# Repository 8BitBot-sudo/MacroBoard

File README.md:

# MacroBoard

So, this is a 12-button and 1 rotary switch macro board. This is useful for clicking on one button for repetitive tasks or for quickly opening an app. The rotary switch would be for controlling volume

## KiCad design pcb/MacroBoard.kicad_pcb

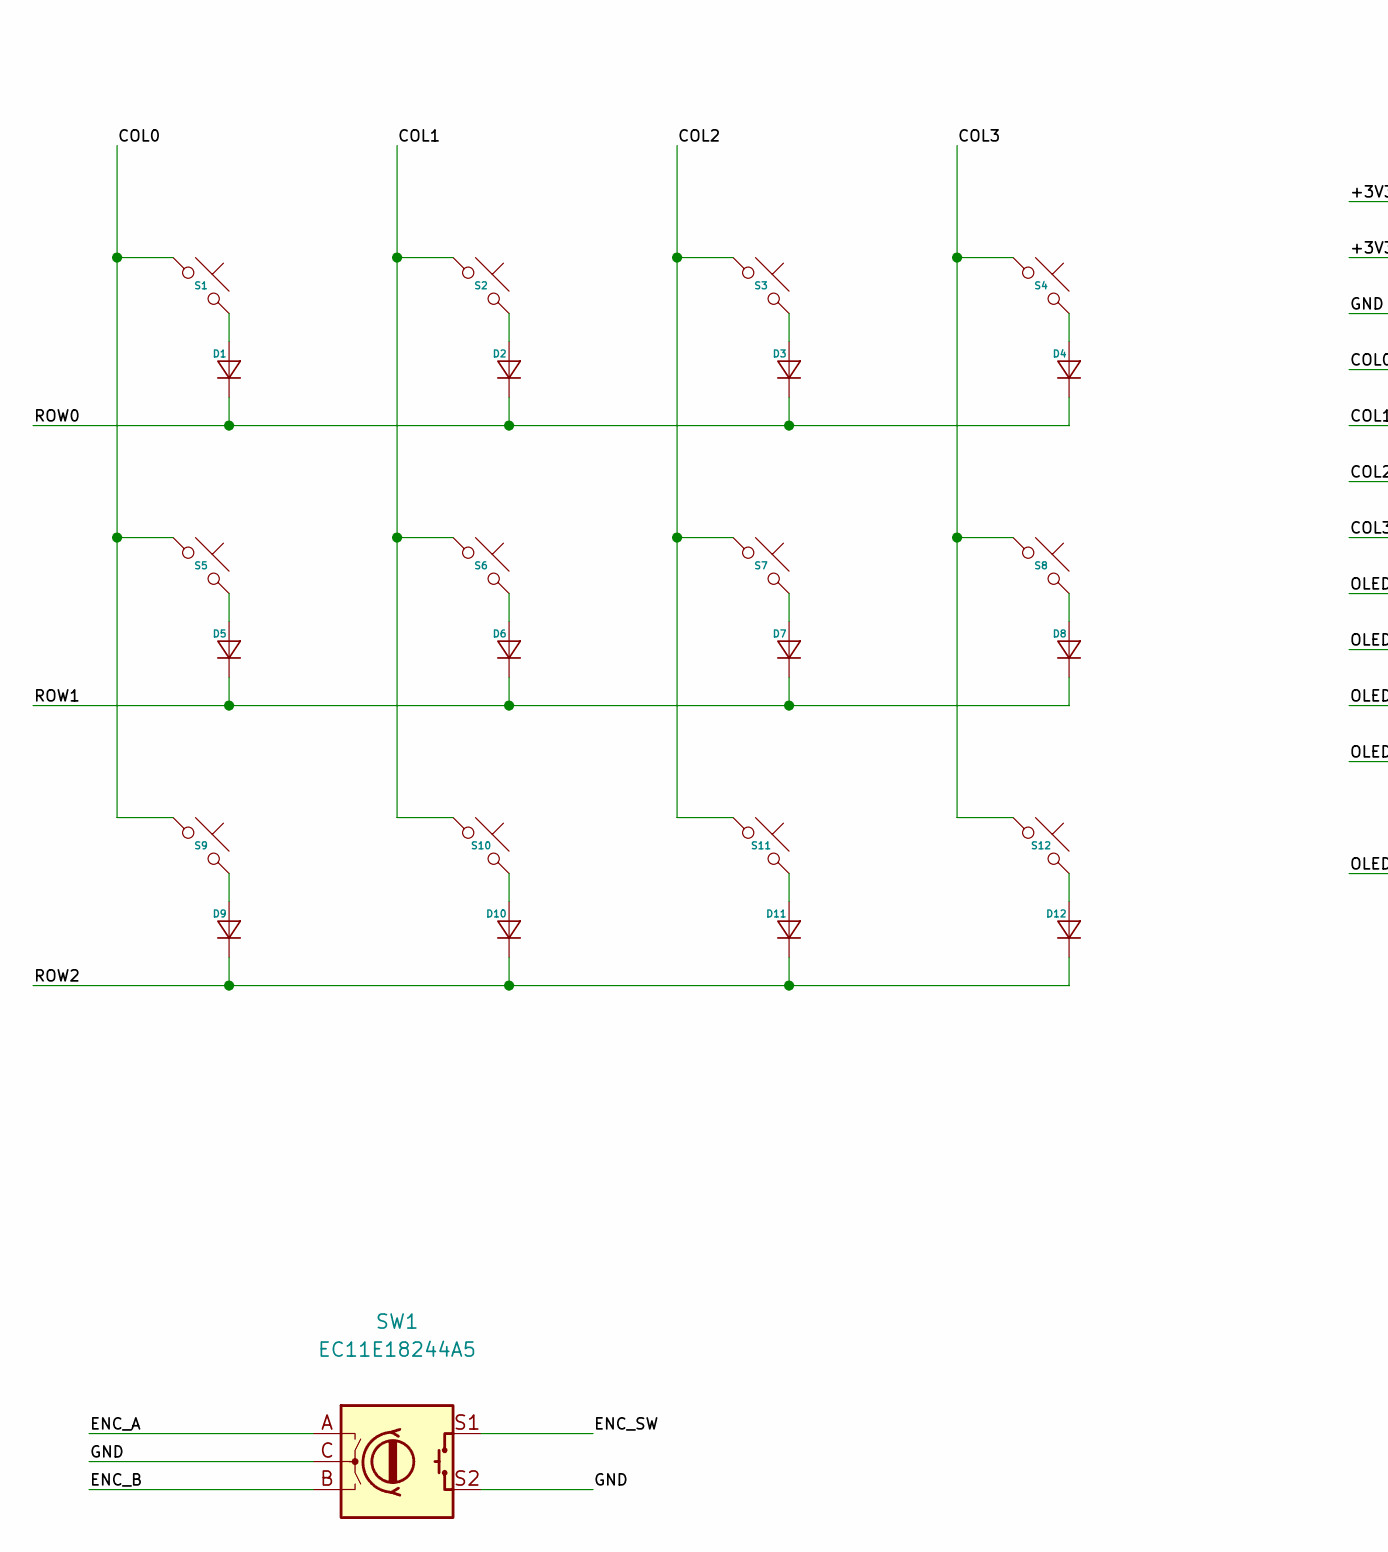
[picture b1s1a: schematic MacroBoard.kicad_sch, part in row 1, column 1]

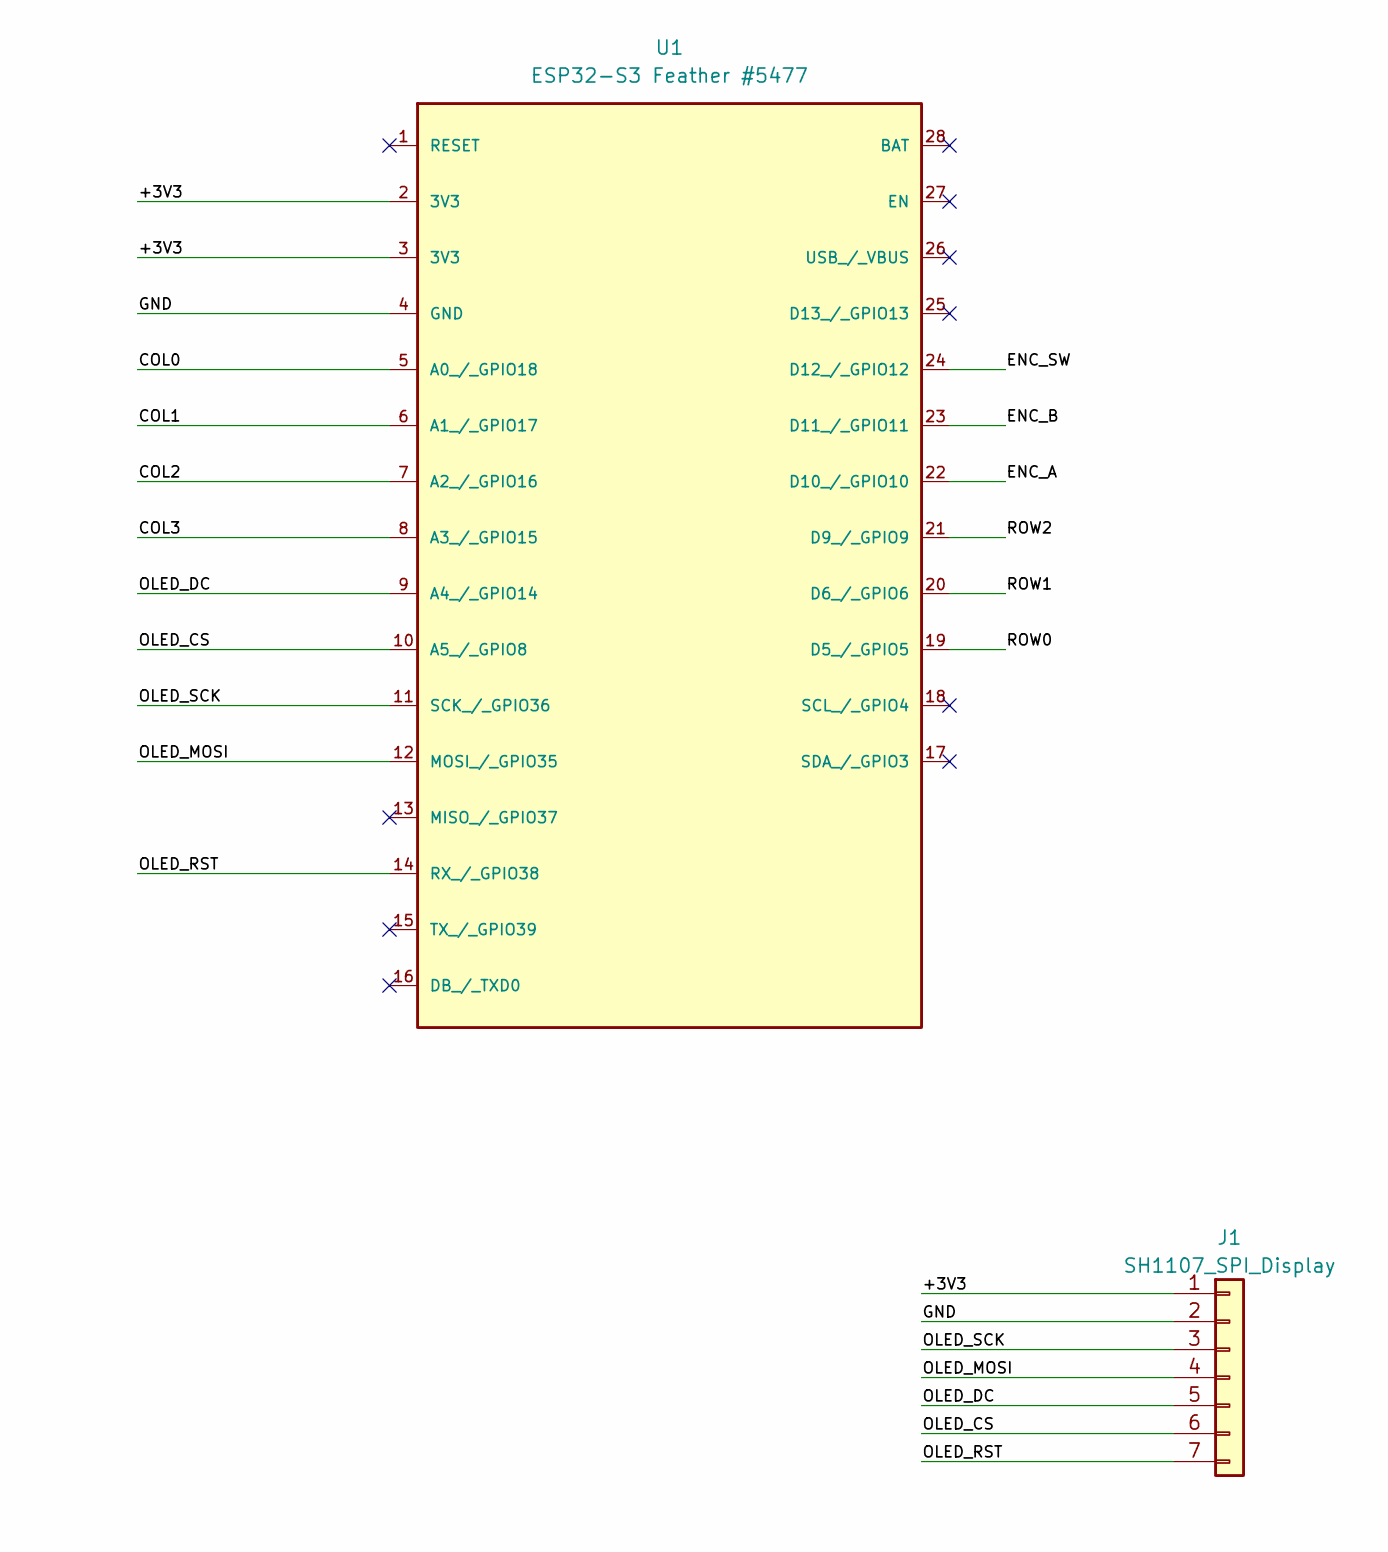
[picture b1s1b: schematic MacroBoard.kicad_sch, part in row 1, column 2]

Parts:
D1, D2, D3, D4, D5, D6, D7, D8, D9, D10, D11, D12: 1N4148; D_DO-35_SOD27_P7.62mm_Horizontal
J1: SH1107_SPI_Display; PinHeader_1x07_P2.54mm_Vertical
S1, S2, S3, S4, S5, S6, S7, S8, S9, S10, S11, S12: Cherry_MX; SW_Cherry_MX_1.00u_PCB
SW1: EC11E18244A5; RotaryEncoder_Alps_EC11E-Switch_Vertical_H20mm
U1: ESP32-S3 Feather #5477; Adafruit_Feather

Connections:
/+3V3: J1.1, U1.2 (3V3), U1.3 (3V3)
/COL0: S1.1, S5.1, S9.1, U1.5 (A0_/_GPIO18)
/COL1: S2.1, S6.1, S10.1, U1.6 (A1_/_GPIO17)
/COL2: S3.1, S7.1, S11.1, U1.7 (A2_/_GPIO16)
/COL3: S4.1, S8.1, S12.1, U1.8 (A3_/_GPIO15)
/ENC_A: SW1.A, U1.22 (D10_/_GPIO10)
/ENC_B: SW1.B, U1.23 (D11_/_GPIO11)
/ENC_SW: SW1.S1, U1.24 (D12_/_GPIO12)
/GND: J1.2, SW1.C, SW1.S2, U1.4 (GND)
/OLED_CS: J1.6, U1.10 (A5_/_GPIO8)
/OLED_DC: J1.5, U1.9 (A4_/_GPIO14)
/OLED_MOSI: J1.4, U1.12 (MOSI_/_GPIO35)
/OLED_RST: J1.7, U1.14 (RX_/_GPIO38)
/OLED_SCK: J1.3, U1.11 (SCK_/_GPIO36)
/ROW0: D1.1 (K), D2.1 (K), D3.1 (K), D4.1 (K), U1.19 (D5_/_GPIO5)
/ROW1: D5.1 (K), D6.1 (K), D7.1 (K), D8.1 (K), U1.20 (D6_/_GPIO6)
/ROW2: D9.1 (K), D10.1 (K), D11.1 (K), D12.1 (K), U1.21 (D9_/_GPIO9)
unnamed: D1.2 (A), S1.2
unnamed: D2.2 (A), S2.2
unnamed: D3.2 (A), S3.2
unnamed: D4.2 (A), S4.2
unnamed: D5.2 (A), S5.2
unnamed: D6.2 (A), S6.2
unnamed: D7.2 (A), S7.2
unnamed: D8.2 (A), S8.2
unnamed: D9.2 (A), S9.2
unnamed: D10.2 (A), S10.2
unnamed: D11.2 (A), S11.2
unnamed: D12.2 (A), S12.2

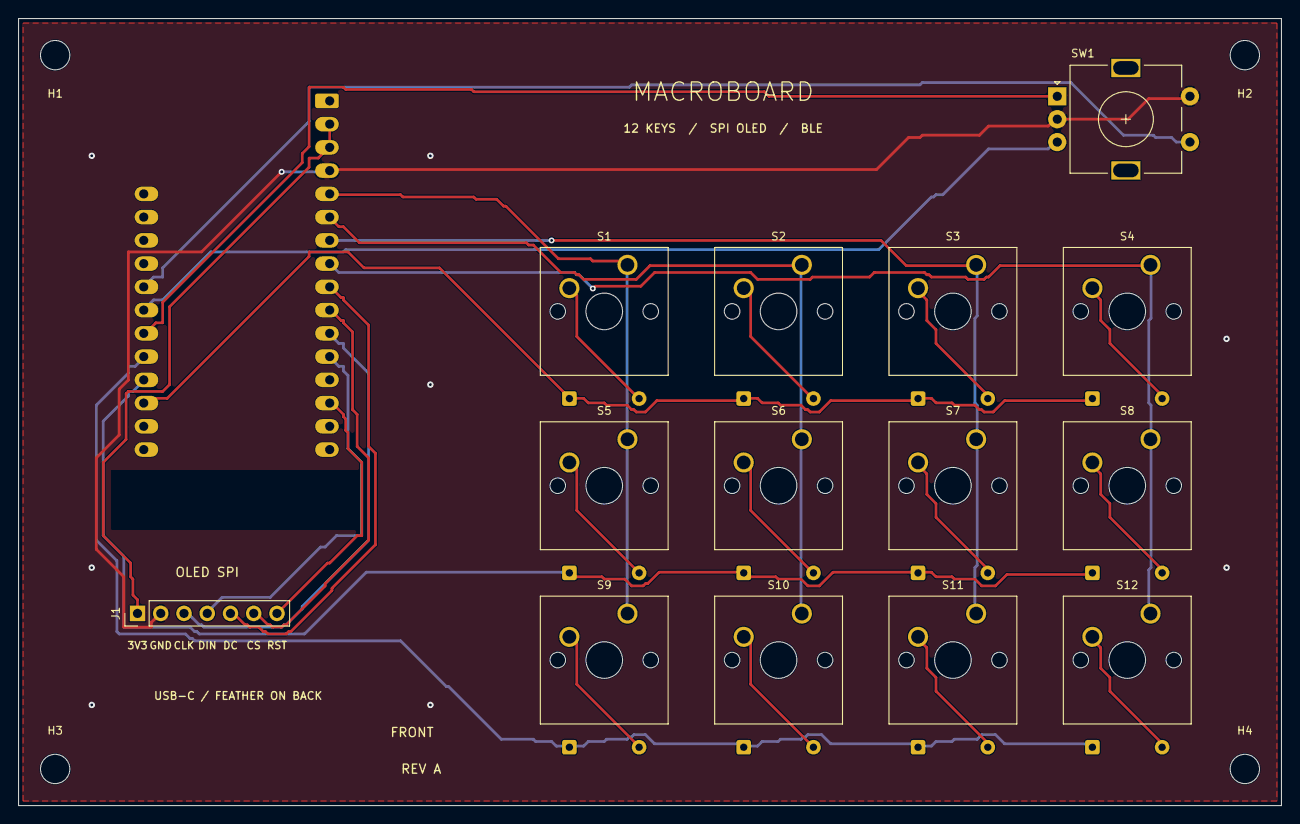
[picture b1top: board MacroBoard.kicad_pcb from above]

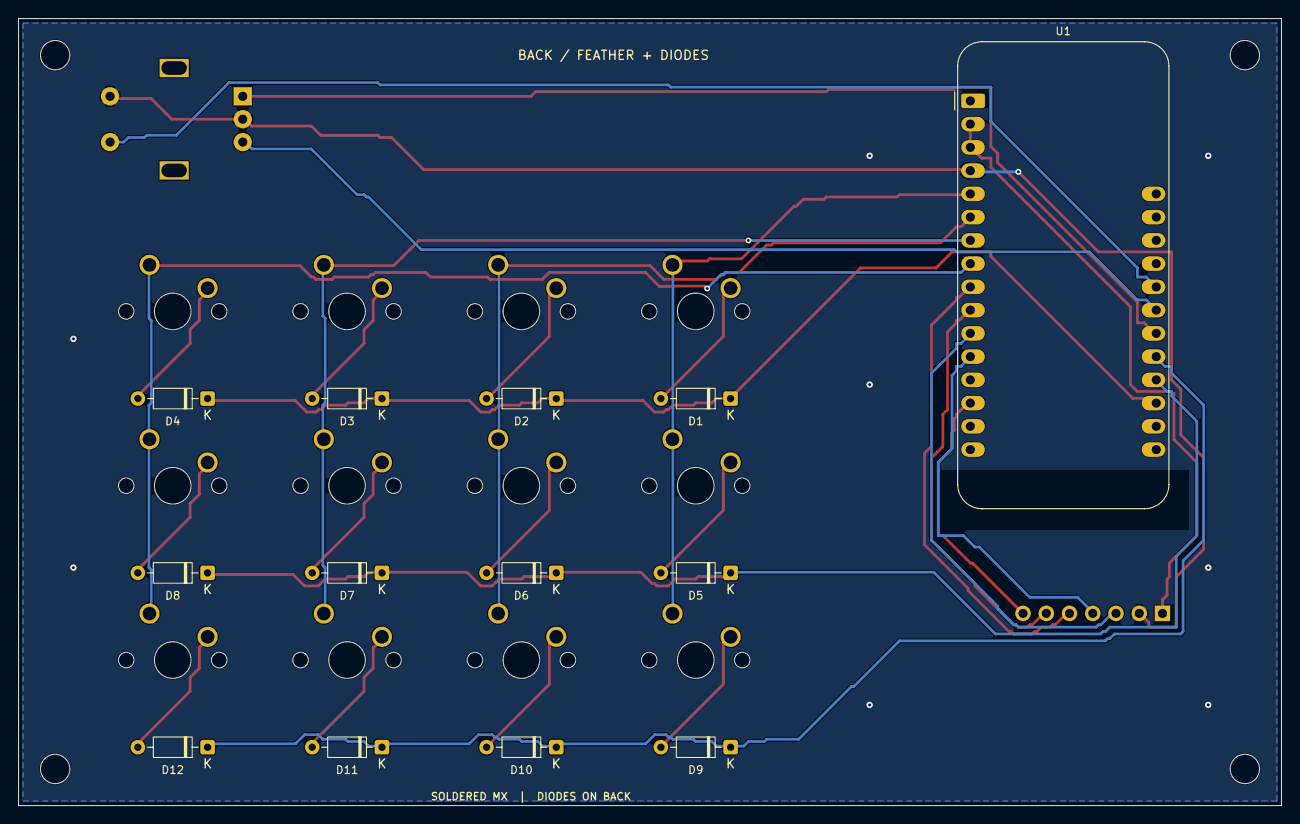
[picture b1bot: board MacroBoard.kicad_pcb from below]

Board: 2 copper layers, 138.0 x 86.0 mm, 31 parts (13 on the bottom side), 29 nets.

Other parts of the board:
H1, H2, H3, H4: M3 mounting hole; MountingHole_3.2mm_M3
